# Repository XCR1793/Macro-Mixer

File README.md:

# Macro Mixer
A DIY Streamdeck alternative for a custom configurable macro board with dials, compatible with commercially available switches (Cherry MX Hotswappable). Reverse mounted under key lighting is also added for both debugging and aesthetics whilst allowing the top side of the board to remain clean and flush.

## Features
* 15x Individually addressable n key rollover switches 
* 6x 12 bit resolution dials
* Addressable underglow lighting for every key and dial
* Easy Key assignment via the software

## [Hardware](/Hardware/README.md)
The case is 3D printed in white PLA plastic however other colour work too. The STLs and Steps are provided in the hardware folder.

## [Software](/Software/README.md)
Using PlatformIO and buildin ESP32 libraries, I have made an easy way to configure what keys are assigned to what key-combo.

## [Embedded](/Embedded/README.md)
Although the currently fabricated PCB has some mistakes, I have modified the KiCAD files to account for this. The embedded circuit is a relatively dense board requiring a steady hand and hotplate.

## Roadmap
* Milestones: Completed Version 1.0
* Work In Progress: Easier software configuration
* Work In Progress: Potentiometers configuration
* Planned: Removing the boot button and using the switch as the the boot switch

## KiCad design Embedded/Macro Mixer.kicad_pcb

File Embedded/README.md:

# Macro Mixer - Embedded
The Wroom32 S3 module is the core of this build as there were just enough pins to hook up all n key rollover switches along with the 6 adc potentiometers. Currently there is a boot button which can be accessed through a hole at the bottom of the case and must be pressed whilst plugging in the board for it to enter boot mode. This will be changed in the future however for it to be the first key so this hole is no longer required and is less of a hastle to enter boot mode.

The Addressable LEDS are reverse mounted such that the top of the pcb will remain flush other than the soldered in potentiometers. This allows easy mounting of components such as the 3D printed case and other accessories that a user may customise their build with. The design of the circuit also allows all (except the potentiometers), to be placed on the bottom side of the pcb and be hotplatted in one go.

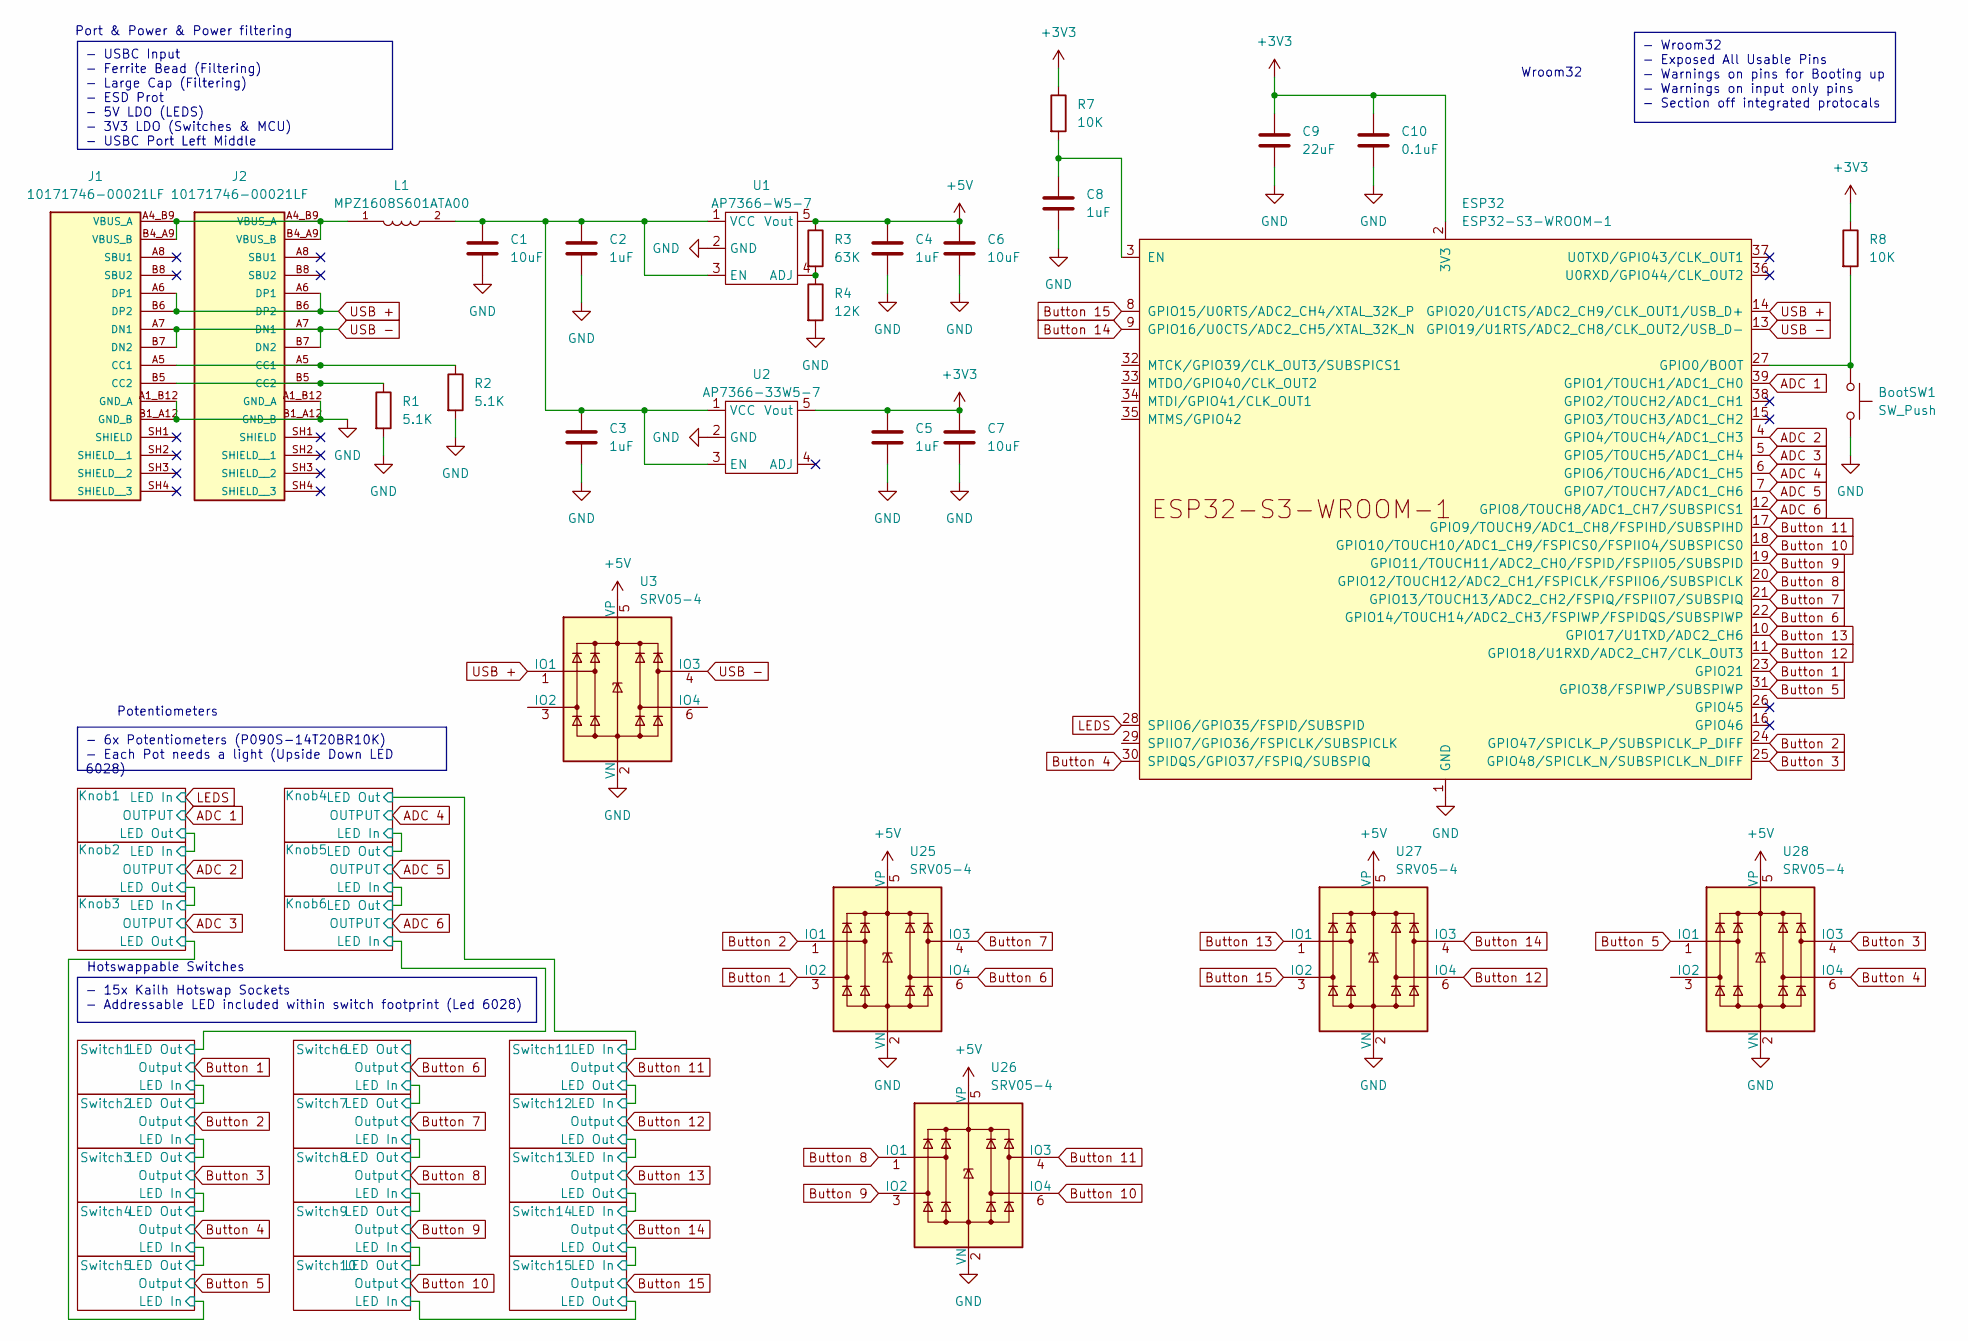
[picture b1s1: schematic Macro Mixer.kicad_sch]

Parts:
BootSW1: SW_Push; Button-R-667843
C1, C6, C7: 10uF; C_0603_1608Metric
C2, C3, C4, C5: 1uF; R_0603_1608Metric
C8: 1uF; C_0603_1608Metric
C9: 22uF; C_1206_3216Metric_Pad1.33x1.80mm_HandSolder
C10: 0.1uF; C_0603_1608Metric
ESP32: ESP32-S3-WROOM-1
J1, J2: 10171746-00021LF; AMPHENOL_10171746-00021LF; PARTREV A
L1: MPZ1608S601ATA00; INDC1608X95N
R1, R2: 5.1K; R_0603_1608Metric
R3: 63K; R_0603_1608Metric
R4: 12K; R_0603_1608Metric
R7, R8: 10K; R_0603_1608Metric
U1: AP7366-W5-7; AP7366
U2: AP7366-33W5-7; AP7366
U3, U25, U26, U27, U28: SRV05-4; SOT-23-6

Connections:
+3V3: C5.1, C7.1, C9.1, C10.1, ESP32.2 (3V3), R7.1, R8.1, U2.5 (Vout); also elsewhere on the board
+5V: C4.1, C6.1, R3.1, U1.5 (Vout), U3.5 (VP), U25.5 (VP), U26.5 (VP), U27.5 (VP), U28.5 (VP); also elsewhere on the board
ADC 1: ESP32.39 (GPIO1/TOUCH1/ADC1_CH0); also elsewhere on the board
ADC 2: ESP32.4 (GPIO4/TOUCH4/ADC1_CH3); also elsewhere on the board
ADC 3: ESP32.5 (GPIO5/TOUCH5/ADC1_CH4); also elsewhere on the board
ADC 4: ESP32.6 (GPIO6/TOUCH6/ADC1_CH5); also elsewhere on the board
ADC 5: ESP32.7 (GPIO7/TOUCH7/ADC1_CH6); also elsewhere on the board
ADC 6: ESP32.12 (GPIO8/TOUCH8/ADC1_CH7/SUBSPICS1); also elsewhere on the board
Button 1: ESP32.23 (GPIO21), U25.3 (IO2); also elsewhere on the board
Button 2: ESP32.24 (GPIO47/SPICLK_P/SUBSPICLK_P_DIFF), U25.1 (IO1); also elsewhere on the board
Button 3: ESP32.25 (GPIO48/SPICLK_N/SUBSPICLK_N_DIFF), U28.4 (IO3); also elsewhere on the board
Button 4: ESP32.30 (SPIDQS/GPIO37/FSPIQ/SUBSPIQ), U28.6 (IO4); also elsewhere on the board
Button 5: ESP32.31 (GPIO38/FSPIWP/SUBSPIWP), U28.1 (IO1); also elsewhere on the board
Button 6: ESP32.22 (GPIO14/TOUCH14/ADC2_CH3/FSPIWP/FSPIDQS/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), U25.6 (IO4); also elsewhere on the board
Button 7: ESP32.21 (GPIO13/TOUCH13/ADC2_CH2/FSPIQ/FSPIIO7/S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), U25.4 (IO3); also elsewhere on the board
Button 8: ESP32.20 (GPIO12/TOUCH12/ADC2_CH1/FSPICLK/FSPIIO6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), U26.1 (IO1); also elsewhere on the board
Button 9: ESP32.19 (GPIO11/TOUCH11/ADC2_CH0/FSPID/FSPIIO5/S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), U26.3 (IO2); also elsewhere on the board
Button 10: ESP32.18 (GPIO10/TOUCH10/ADC1_CH9/FSPICS0/FSPIIO4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), U26.6 (IO4); also elsewhere on the board
Button 11: ESP32.17 (GPIO9/TOUCH9/ADC1_CH8/FSPIHD/SUBSPIHD), U26.4 (IO3); also elsewhere on the board
Button 12: ESP32.11 (GPIO18/U1RXD/ADC2_CH7/CLK_OUT3), U27.6 (IO4); also elsewhere on the board
Button 13: ESP32.10 (GPIO17/U1TXD/ADC2_CH6), U27.1 (IO1); also elsewhere on the board
Button 14: ESP32.9 (GPIO16/U0CTS/ADC2_CH5/XTAL_32K_N), U27.4 (IO3); also elsewhere on the board
Button 15: ESP32.8 (GPIO15/U0RTS/ADC2_CH4/XTAL_32K_P), U27.3 (IO2); also elsewhere on the board
GND: BootSW1.2, C1.2, C2.2, C3.2, C4.2, C5.2, C6.2, C7.2, C8.2, C9.2, C10.2, ESP32.1 (GND), ESP32.40 (GND), ESP32.41 (GND), J1.A1_B12 (GND_A), J1.B1_A12 (GND_B), J2.A1_B12 (GND_A), J2.B1_A12 (GND_B), R1.2, R2.2, R4.2, U1.2 (GND), U2.2 (GND), U3.2 (VN), U25.2 (VN), U26.2 (VN), U27.2 (VN), U28.2 (VN); also elsewhere on the board
LEDS: ESP32.28 (SPIIO6/GPIO35/FSPID/SUBSPID); also elsewhere on the board
unnamed: C8.1, ESP32.3 (EN), R7.2
unnamed: BootSW1.1, ESP32.27 (GPIO0/BOOT), R8.2
unnamed: J1.A5 (CC1), J2.A5 (CC1), R2.1
unnamed: J1.B5 (CC2), J2.B5 (CC2), R1.1
unnamed: J1.A4_B9 (VBUS_A), J1.B4_A9 (VBUS_B), J2.A4_B9 (VBUS_A), J2.B4_A9 (VBUS_B), L1.1
unnamed: R3.2, R4.1, U1.4 (ADJ)
unnamed: C1.1, C2.1, C3.1, L1.2, U1.1 (VCC), U1.3 (EN), U2.1 (VCC), U2.3 (EN)
USB +: ESP32.14 (GPIO20/U1CTS/ADC2_CH9/CLK_OUT1/USB_D+), J1.A6 (DP1), J1.B6 (DP2), J2.A6 (DP1), J2.B6 (DP2), U3.1 (IO1)
USB -: ESP32.13 (GPIO19/U1RTS/ADC2_CH8/CLK_OUT2/USB_D-), J1.A7 (DN1), J1.B7 (DN2), J2.A7 (DN1), J2.B7 (DN2), U3.4 (IO3)

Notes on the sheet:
- 6x Potentiometers (P090S-14T20BR10K) - Each Pot needs a light (Upside Down LED 6028)
- USBC Input - Ferrite Bead (Filtering) - Large Cap (Filtering) - ESD Prot - 5V LDO (LEDS) - 3V3 LDO (Switches & MCU) - USBC Port Left Middle
- Wroom32 - Exposed All Usable Pins - Warnings on pins for Booting up - Warnings on input only pins - Section off integrated protocals
- 15x Kailh Hotswap Sockets - Addressable LED included within switch footprint (Led 6028)
Port & Power & Power filtering
Wroom32
Potentiometers
Hotswappable Switches

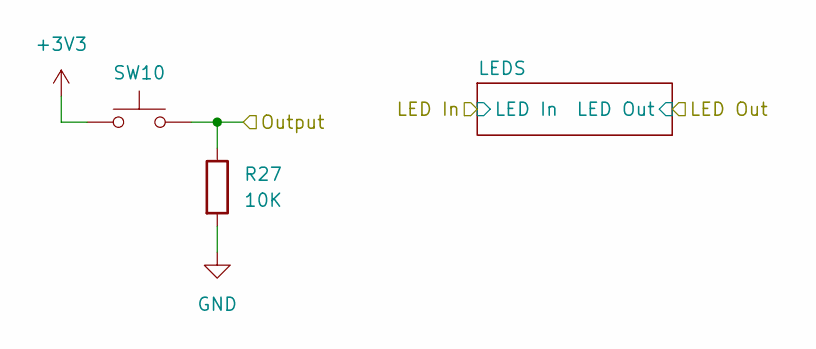
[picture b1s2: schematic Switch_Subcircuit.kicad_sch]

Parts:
R27: 10K; R_0603_1608Metric
SW10: Switch; Hotswap_MX_1.00u

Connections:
+3V3: SW10.1; also elsewhere on the board
Button 10: R27.1, SW10.2; also elsewhere on the board
GND: R27.2; also elsewhere on the board

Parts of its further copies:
R9, R10, R11, R12, R13, R14, R15, R16, R26, R28, R29, R30, R31, R32: 10K; R_0603_1608Metric
SW1, SW2, SW3, SW4, SW5, SW6, SW7, SW8, SW9, SW11, SW12, SW13, SW14, SW15: Switch; Hotswap_MX_1.00u

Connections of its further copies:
+3V3: SW1.1, SW2.1, SW3.1, SW4.1, SW5.1, SW6.1, SW7.1, SW8.1, SW9.1, SW11.1, SW12.1, SW13.1, SW14.1, SW15.1; also elsewhere on the board
Button 1: R9.1, SW1.2; also elsewhere on the board
Button 2: R10.1, SW2.2; also elsewhere on the board
Button 3: R11.1, SW3.2; also elsewhere on the board
Button 4: R12.1, SW4.2; also elsewhere on the board
Button 5: R13.1, SW5.2; also elsewhere on the board
Button 6: R14.1, SW6.2; also elsewhere on the board
Button 7: R15.1, SW7.2; also elsewhere on the board
Button 8: R16.1, SW8.2; also elsewhere on the board
Button 9: R26.1, SW9.2; also elsewhere on the board
Button 11: R28.1, SW11.2; also elsewhere on the board
Button 12: R29.1, SW12.2; also elsewhere on the board
Button 13: R30.1, SW13.2; also elsewhere on the board
Button 14: R31.1, SW14.2; also elsewhere on the board
Button 15: R32.1, SW15.2; also elsewhere on the board
GND: R9.2, R10.2, R11.2, R12.2, R13.2, R14.2, R15.2, R16.2, R26.2, R28.2, R29.2, R30.2, R31.2, R32.2; also elsewhere on the board

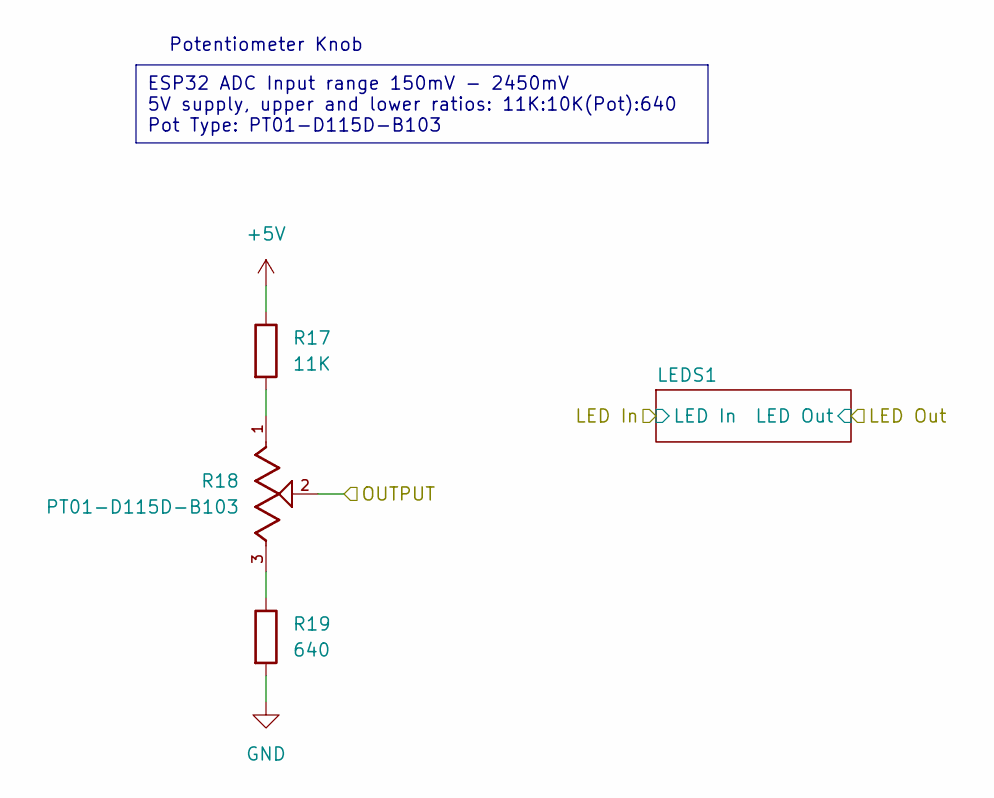
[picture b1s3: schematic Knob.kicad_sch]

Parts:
R17: 11K; R_0603_1608Metric
R18: PT01-D115D-B103; TRIM_PT01-D115D-B103; PARTREV 1.0
R19: 640; R_0603_1608Metric

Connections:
+5V: R17.1; also elsewhere on the board
ADC 1: R18.2; also elsewhere on the board
GND: R19.2; also elsewhere on the board
unnamed: R17.2, R18.1
unnamed: R18.3, R19.1

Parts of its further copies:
R20, R23, R33, R36, R39: 11K; R_0603_1608Metric
R21, R24, R34, R37, R40: PT01-D115D-B103; TRIM_PT01-D115D-B103; PARTREV 1.0
R22, R25, R35, R38, R41: 640; R_0603_1608Metric

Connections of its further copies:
+5V: R20.1, R23.1, R33.1, R36.1, R39.1; also elsewhere on the board
ADC 2: R21.2; also elsewhere on the board
ADC 3: R24.2; also elsewhere on the board
ADC 4: R34.2; also elsewhere on the board
ADC 5: R37.2; also elsewhere on the board
ADC 6: R40.2; also elsewhere on the board
GND: R22.2, R25.2, R35.2, R38.2, R41.2; also elsewhere on the board
unnamed: R20.2, R21.1
unnamed: R21.3, R22.1
unnamed: R23.2, R24.1
unnamed: R24.3, R25.1
unnamed: R33.2, R34.1
unnamed: R34.3, R35.1
unnamed: R36.2, R37.1
unnamed: R37.3, R38.1
unnamed: R39.2, R40.1
unnamed: R40.3, R41.1

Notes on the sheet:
ESP32 ADC Input range 150mV - 2450mV 5V supply, upper and lower ratios: 11K:10K(Pot):640 Pot Type: PT01-D115D-B103
Potentiometer Knob

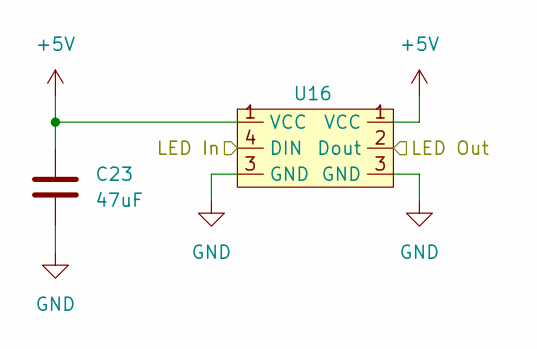
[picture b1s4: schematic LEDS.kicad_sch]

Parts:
C23: 47uF; C_0603_1608Metric
U16: 6028_Reverse_Mount

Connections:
+5V: C23.1, U16.1 (VCC); also elsewhere on the board
/Switch10/LED In: U16.4 (DIN); also elsewhere on the board
/Switch10/LED Out: U16.2 (Dout); also elsewhere on the board
GND: C23.2, U16.3 (GND); also elsewhere on the board

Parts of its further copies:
C11, C12, C13, C14, C15, C16, C17, C18, C19, C20, C21, C22, C24, C25, C26, C27, C28, C29, C30, C31: 47uF; C_0603_1608Metric
U4, U5, U6, U7, U8, U9, U10, U11, U12, U13, U14, U15, U17, U18, U19, U20, U21, U22, U23, U24: 6028_Reverse_Mount

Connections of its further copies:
+5V: C11.1, C12.1, C13.1, C14.1, C15.1, C16.1, C17.1, C18.1, C19.1, C20.1, C21.1, C22.1, C24.1, C25.1, C26.1, C27.1, C28.1, C29.1, C30.1, C31.1, U4.1 (VCC), U5.1 (VCC), U6.1 (VCC), U7.1 (VCC), U8.1 (VCC), U9.1 (VCC), U10.1 (VCC), U11.1 (VCC), U12.1 (VCC), U13.1 (VCC), U14.1 (VCC), U15.1 (VCC), U17.1 (VCC), U18.1 (VCC), U19.1 (VCC), U20.1 (VCC), U21.1 (VCC), U22.1 (VCC), U23.1 (VCC), U24.1 (VCC); also elsewhere on the board
/Knob1/LED Out: U11.2 (Dout), U12.4 (DIN)
/Knob2/LED Out: U12.2 (Dout), U13.4 (DIN)
/Knob3/LED Out: U7.4 (DIN), U13.2 (Dout)
/Knob4/LED In: U22.4 (DIN), U23.2 (Dout)
/Knob4/LED Out: U17.4 (DIN), U22.2 (Dout)
/Knob5/LED In: U23.4 (DIN), U24.2 (Dout)
/Knob6/LED In: U14.2 (Dout), U24.4 (DIN)
/Switch1/LED In: U4.2 (Dout), U14.4 (DIN)
/Switch2/LED In: U4.4 (DIN), U5.2 (Dout)
/Switch3/LED In: U5.4 (DIN), U6.2 (Dout)
/Switch4/LED In: U6.4 (DIN), U7.2 (Dout)
/Switch6/LED In: U8.4 (DIN), U9.2 (Dout)
/Switch6/LED Out: U8.2 (Dout)
/Switch7/LED In: U9.4 (DIN), U10.2 (Dout)
/Switch8/LED In: U10.4 (DIN), U15.2 (Dout)
/Switch10/LED In: U21.2 (Dout); also elsewhere on the board
/Switch10/LED Out: U15.4 (DIN); also elsewhere on the board
/Switch11/LED Out: U17.2 (Dout), U18.4 (DIN)
/Switch12/LED Out: U18.2 (Dout), U19.4 (DIN)
/Switch13/LED Out: U19.2 (Dout), U20.4 (DIN)
/Switch14/LED Out: U20.2 (Dout), U21.4 (DIN)
GND: C11.2, C12.2, C13.2, C14.2, C15.2, C16.2, C17.2, C18.2, C19.2, C20.2, C21.2, C22.2, C24.2, C25.2, C26.2, C27.2, C28.2, C29.2, C30.2, C31.2, U4.3 (GND), U5.3 (GND), U6.3 (GND), U7.3 (GND), U8.3 (GND), U9.3 (GND), U10.3 (GND), U11.3 (GND), U12.3 (GND), U13.3 (GND), U14.3 (GND), U15.3 (GND), U17.3 (GND), U18.3 (GND), U19.3 (GND), U20.3 (GND), U21.3 (GND), U22.3 (GND), U23.3 (GND), U24.3 (GND); also elsewhere on the board
LEDS: U11.4 (DIN); also elsewhere on the board

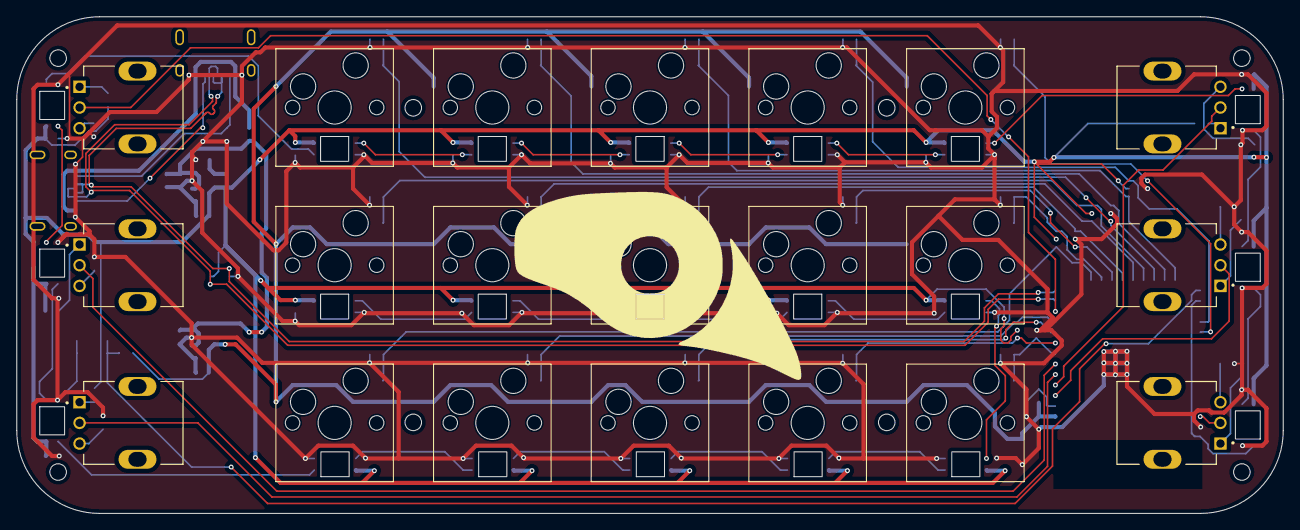
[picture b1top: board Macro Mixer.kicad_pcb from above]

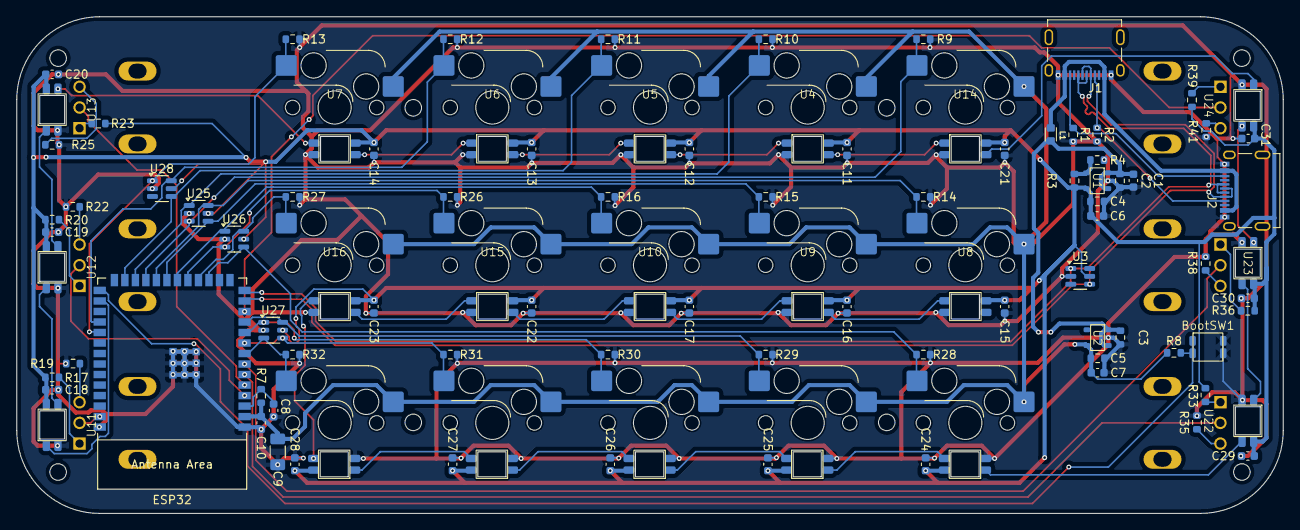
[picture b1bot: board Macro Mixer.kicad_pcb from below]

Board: 2 copper layers, 152.9 x 60.0 mm, 118 parts (97 on the bottom side), 66 nets.

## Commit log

2024-12-12 Uploaded Files & Added Key Macros
2024-12-13 All keys now fully configurable with any standard keyboard key combination
2024-12-25 Added Documentation
